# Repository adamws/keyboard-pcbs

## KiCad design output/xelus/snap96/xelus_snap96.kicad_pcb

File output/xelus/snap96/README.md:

## xelus/snap96/xelus_snap96

[layout](xelus_snap96-kle.json) - [PCB](xelus_snap96.kicad_pcb)

{:loading="lazy"}

[Open in keyboard-layout-editor](http://www.keyboard-layout-editor.com/##@_name=Snap96;&@_x:2.75&y:1&c=#888888;&=0,0&_c=#aaaaaa;&=0,1&=0,2&=0,3&=0,4&=0,5&=0,6&=0,7&=0,8&=0,9&=6,0&=6,1&=6,2&=6,3&=6,4&=6,5&=6,6&=6,7&=6,8;&@_x:2.75&c=#cccccc;&=1,0&=1,1&=1,2&=1,3&=1,4&=1,5&=1,6&=1,7&=1,8&=1,9&=7,0&=7,1&=7,2&_c=#aaaaaa&w:2;&=7,4%0A%0A%0A0,0&=7,5&=7,6&=7,7&=7,8;&@_x:2.75&w:1.5;&=2,0&_c=#cccccc;&=2,1&=2,2&=2,3&=2,4&=2,5&=2,6&=2,7&=2,8&=2,9&=8,0&=8,1&=8,2&_w:1.5;&=8,4%0A%0A%0A1,0&=8,5&=8,6&=8,7&_c=#aaaaaa&h:2;&=9,8%0A%0A%0A5,0;&@_x:2.75&w:1.75;&=3,0&_c=#cccccc;&=3,1&=3,2&=3,3&=3,4&=3,5&=3,6&=3,7&=3,8&=3,9&=9,0&=9,1&_c=#888888&w:2.25;&=9,3%0A%0A%0A1,0&_c=#cccccc;&=9,5&=9,6&=9,7;&@_x:2.75&c=#aaaaaa&w:2.25;&=4,0%0A%0A%0A2,0&_c=#cccccc;&=4,2&=4,3&=4,4&=4,5&=4,6&=4,7&=4,8&=4,9&=10,0&=10,1%0A%0A%0A3,0&_c=#aaaaaa&w:1.75;&=10,3%0A%0A%0A3,0&=10,4%0A%0A%0A3,0&_c=#cccccc;&=10,5&=10,6&=10,7&_c=#888888&h:2;&=11,8%0A%0A%0A6,0;&@_x:2.75&c=#aaaaaa&w:1.5;&=5,0%0A%0A%0A4,0&=5,1%0A%0A%0A4,0&_w:1.5;&=5,2%0A%0A%0A4,0&_c=#cccccc&w:7;&=5,6%0A%0A%0A4,0&_c=#aaaaaa&w:1.5;&=11,1%0A%0A%0A4,0&=11,3%0A%0A%0A4,0&_w:1.5;&=11,4%0A%0A%0A4,0&_c=#cccccc;&=11,5%0A%0A%0A7,0&=11,6%0A%0A%0A7,0&=11,7%0A%0A%0A7,0;&@_x:15.75&y:-7;&=7,3%0A%0A%0A0,1&=7,4%0A%0A%0A0,1;&@_x:23.25&y:1&c=#888888&w:1.25&h:2&w2:1.5&h2:1&x2:-0.25;&=8,4%0A%0A%0A1,1;&@_x:22.25&c=#cccccc;&=9,3%0A%0A%0A1,1&_x:3.25&c=#aaaaaa;&=8,8%0A%0A%0A5,1;&@_x:22.25&c=#cccccc;&=10,1%0A%0A%0A3,1&_c=#aaaaaa&w:2.75;&=10,3%0A%0A%0A3,1&_x:0.5;&=8,9%0A%0A%0A5,1;&@_w:1.25;&=4,0%0A%0A%0A2,1&_c=#cccccc;&=4,1%0A%0A%0A2,1&_x:20.0&c=#aaaaaa&w:1.75;&=10,1%0A%0A%0A3,2&_c=#cccccc;&=10,3%0A%0A%0A3,2&=10,4%0A%0A%0A3,2&_x:0.5&c=#aaaaaa;&=10,8%0A%0A%0A6,1;&@_x:26.5;&=11,8%0A%0A%0A6,1;&@_x:2.75&y:0.5&w:1.25;&=5,0%0A%0A%0A4,1&_w:1.25;&=5,1%0A%0A%0A4,1&_w:1.25;&=5,2%0A%0A%0A4,1&_c=#cccccc&w:6.25;&=5,6%0A%0A%0A4,1&_c=#aaaaaa&w:1.25;&=11,0%0A%0A%0A4,1&_w:1.25;&=11,1%0A%0A%0A4,1&_w:1.25;&=11,3%0A%0A%0A4,1&_w:1.25;&=11,4%0A%0A%0A4,1&_x:0.5&c=#cccccc&w:2;&=11,5%0A%0A%0A7,1&=11,7%0A%0A%0A7,1;&@_x:2.75&c=#aaaaaa&w:1.25;&=5,0%0A%0A%0A4,2&_w:1.25;&=5,1%0A%0A%0A4,2&_w:1.25;&=5,2%0A%0A%0A4,2&_c=#cccccc&w:2.75;&=5,5%0A%0A%0A4,2&_w:1.25;&=5,6%0A%0A%0A4,2&_w:2.25;&=5,9%0A%0A%0A4,2&_c=#aaaaaa&w:1.25;&=11,0%0A%0A%0A4,2&_w:1.25;&=11,1%0A%0A%0A4,2&_w:1.25;&=11,3%0A%0A%0A4,2&_w:1.25;&=11,4%0A%0A%0A4,2&_x:0.5&c=#cccccc;&=11,5%0A%0A%0A7,2&_w:2;&=11,7%0A%0A%0A7,2;&@_x:2.75&c=#aaaaaa&w:1.25;&=5,0%0A%0A%0A4,3&_w:1.25;&=5,1%0A%0A%0A4,3&_w:1.25;&=5,2%0A%0A%0A4,3&_c=#cccccc&w:2.25;&=5,5%0A%0A%0A4,3&_w:1.25;&=5,6%0A%0A%0A4,3&_w:2.75;&=5,9%0A%0A%0A4,3&_c=#aaaaaa&w:1.25;&=11,0%0A%0A%0A4,3&_w:1.25;&=11,1%0A%0A%0A4,3&_w:1.25;&=11,3%0A%0A%0A4,3&_w:1.25;&=11,4%0A%0A%0A4,3)

{:loading="lazy"}

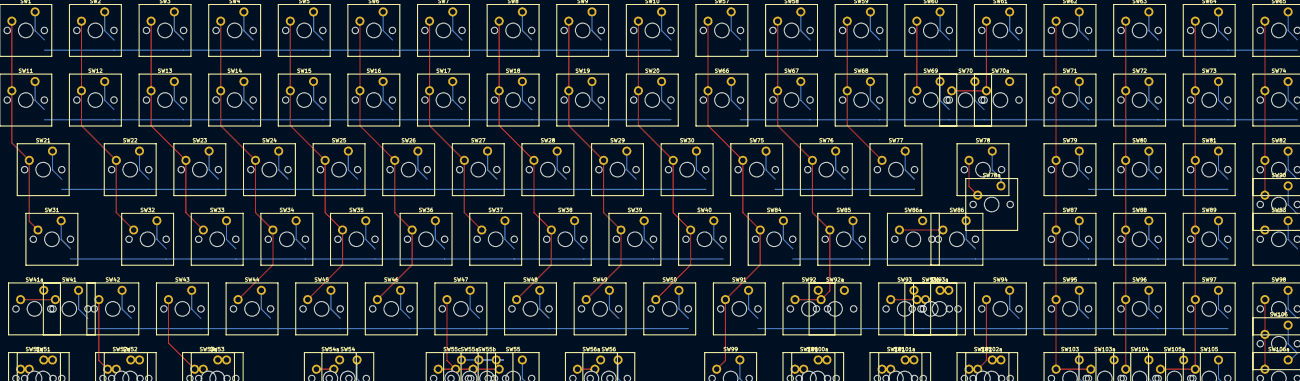
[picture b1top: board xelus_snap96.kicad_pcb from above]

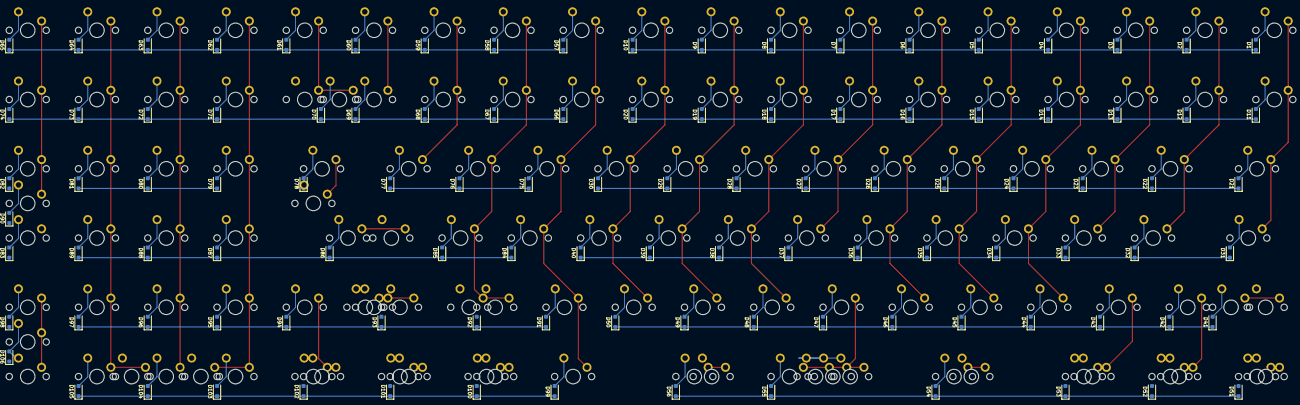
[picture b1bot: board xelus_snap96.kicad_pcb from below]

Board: 2 copper layers, 233 parts (106 on the bottom side), 128 nets.

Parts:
D1, D2, D3, D4, D5, D6, D7, D8, D9, D10, D11, D12, D13, D14, D15, D16, D17, D18, D19, D20, D21, D22, D23, D24, D25, D26, D27, D28, D29, D30, D31, D32, D33, D34, D35, D36, D37, D38, D39, D40, D41, D42, D43, D44, D45, D46, D47, D48, D49, D50, D51, D52, D53, D54, D55, D56, D57, D58, D59, D60, D61, D62, D63, D64, D65, D66, D67, D68, D69, D70, D71, D72, D73, D74, D75, D76, D77, D78, D79, D80, D81, D82, D83, D84, D85, D86, D87, D88, D89, D90, D91, D92, D93, D94, D95, D96, D97, D98, D99, D100, D101, D102, D103, D104, D105, D106: D_SOD-123F
SW1, SW2, SW3, SW4, SW5, SW6, SW7, SW8, SW9, SW10, SW11, SW12, SW13, SW14, SW15, SW16, SW17, SW18, SW19, SW20, SW21, SW22, SW23, SW24, SW25, SW26, SW27, SW28, SW29, SW30, SW31, SW32, SW33, SW34, SW35, SW36, SW37, SW38, SW39, SW40, SW41, SW41a, SW42, SW43, SW44, SW45, SW46, SW47, SW48, SW49, SW50, SW51, SW51a, SW52, SW52a, SW53, SW53a, SW54, SW54a, SW55, SW55a, SW55b, SW55c, SW56, SW56a, SW57, SW58, SW59, SW60, SW61, SW62, SW63, SW64, SW65, SW66, SW67, SW68, SW69, SW70, SW70a, SW71, SW72, SW73, SW74, SW75, SW76, SW77, SW78, SW78a, SW79, SW80, SW81, SW82, SW83, SW84, SW85, SW86, SW86a, SW87, SW88, SW89, SW90, SW91, SW92, SW92a, SW93, SW93a, SW93b, SW94, SW95, SW96, SW97, SW98, SW99, SW100, SW100a, SW101, SW101a, SW102, SW102a, SW103, SW103a, SW104, SW105, SW105a, SW106, SW106a: SW_Cherry_MX_PCB_1.00u

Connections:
COL0: SW1.1, SW11.1, SW21.1, SW31.1, SW41.1, SW41a.1, SW51.1, SW51a.1, SW57.1, SW66.1, SW75.1, SW84.1, SW91.1, SW99.1
COL1: SW2.1, SW12.1, SW22.1, SW32.1, SW42.1, SW52.1, SW52a.1, SW58.1, SW67.1, SW76.1, SW85.1, SW92.1, SW92a.1, SW100.1, SW100a.1
COL2: SW3.1, SW13.1, SW23.1, SW33.1, SW43.1, SW53.1, SW53a.1, SW59.1, SW68.1, SW77.1
COL3: SW4.1, SW14.1, SW24.1, SW34.1, SW44.1, SW60.1, SW69.1, SW86.1, SW86a.1, SW93.1, SW93a.1, SW93b.1, SW101.1, SW101a.1
COL4: SW5.1, SW15.1, SW25.1, SW35.1, SW45.1, SW61.1, SW70.1, SW70a.1, SW78.1, SW78a.1, SW94.1, SW102.1, SW102a.1
COL5: SW6.1, SW16.1, SW26.1, SW36.1, SW46.1, SW54.1, SW54a.1, SW62.1, SW71.1, SW79.1, SW87.1, SW95.1, SW103.1, SW103a.1
COL6: SW7.1, SW17.1, SW27.1, SW37.1, SW47.1, SW55.1, SW55a.1, SW55b.1, SW55c.1, SW63.1, SW72.1, SW80.1, SW88.1, SW96.1, SW104.1
COL7: SW8.1, SW18.1, SW28.1, SW38.1, SW48.1, SW64.1, SW73.1, SW81.1, SW89.1, SW97.1, SW105.1, SW105a.1
COL8: SW9.1, SW19.1, SW29.1, SW39.1, SW49.1, SW65.1, SW74.1, SW82.1, SW90.1, SW98.1, SW106.1, SW106a.1
COL9: SW10.1, SW20.1, SW30.1, SW40.1, SW50.1, SW56.1, SW56a.1, SW83.1
unnamed: D1.2, SW1.2
unnamed: D2.2, SW2.2
unnamed: D3.2, SW3.2
unnamed: D4.2, SW4.2
unnamed: D5.2, SW5.2
unnamed: D6.2, SW6.2
unnamed: D7.2, SW7.2
unnamed: D8.2, SW8.2
unnamed: D9.2, SW9.2
unnamed: D10.2, SW10.2
unnamed: D11.2, SW11.2
unnamed: D12.2, SW12.2
unnamed: D13.2, SW13.2
unnamed: D14.2, SW14.2
unnamed: D15.2, SW15.2
unnamed: D16.2, SW16.2
unnamed: D17.2, SW17.2
unnamed: D18.2, SW18.2
unnamed: D19.2, SW19.2
unnamed: D20.2, SW20.2
unnamed: D21.2, SW21.2
unnamed: D22.2, SW22.2
unnamed: D23.2, SW23.2
unnamed: D24.2, SW24.2
unnamed: D25.2, SW25.2
unnamed: D26.2, SW26.2
unnamed: D27.2, SW27.2
unnamed: D28.2, SW28.2
unnamed: D29.2, SW29.2
unnamed: D30.2, SW30.2
unnamed: D31.2, SW31.2
unnamed: D32.2, SW32.2
unnamed: D33.2, SW33.2
unnamed: D34.2, SW34.2
unnamed: D35.2, SW35.2
unnamed: D36.2, SW36.2
unnamed: D37.2, SW37.2
unnamed: D38.2, SW38.2
unnamed: D39.2, SW39.2
unnamed: D40.2, SW40.2
unnamed: D41.2, SW41.2, SW41a.2
unnamed: D42.2, SW42.2
unnamed: D43.2, SW43.2
unnamed: D44.2, SW44.2
unnamed: D45.2, SW45.2
unnamed: D46.2, SW46.2
unnamed: D47.2, SW47.2
unnamed: D48.2, SW48.2
unnamed: D49.2, SW49.2
unnamed: D50.2, SW50.2
unnamed: D51.2, SW51.2, SW51a.2
unnamed: D52.2, SW52.2, SW52a.2
unnamed: D53.2, SW53.2, SW53a.2
unnamed: D54.2, SW54.2, SW54a.2
unnamed: D55.2, SW55.2, SW55a.2, SW55b.2, SW55c.2
unnamed: D56.2, SW56.2, SW56a.2
unnamed: D57.2, SW57.2
unnamed: D58.2, SW58.2
unnamed: D59.2, SW59.2
unnamed: D60.2, SW60.2
unnamed: D61.2, SW61.2
unnamed: D62.2, SW62.2
unnamed: D63.2, SW63.2
unnamed: D64.2, SW64.2
unnamed: D65.2, SW65.2
unnamed: D66.2, SW66.2
unnamed: D67.2, SW67.2
unnamed: D68.2, SW68.2
unnamed: D69.2, SW69.2
unnamed: D70.2, SW70.2, SW70a.2
unnamed: D71.2, SW71.2
unnamed: D72.2, SW72.2
unnamed: D73.2, SW73.2
unnamed: D74.2, SW74.2
unnamed: D75.2, SW75.2
unnamed: D76.2, SW76.2
unnamed: D77.2, SW77.2
unnamed: D78.2, SW78.2, SW78a.2
unnamed: D79.2, SW79.2
unnamed: D80.2, SW80.2
unnamed: D81.2, SW81.2
unnamed: D82.2, SW82.2
unnamed: D83.2, SW83.2
unnamed: D84.2, SW84.2
unnamed: D85.2, SW85.2
unnamed: D86.2, SW86.2, SW86a.2
unnamed: D87.2, SW87.2
unnamed: D88.2, SW88.2
unnamed: D89.2, SW89.2
unnamed: D90.2, SW90.2
unnamed: D91.2, SW91.2
unnamed: D92.2, SW92.2, SW92a.2
unnamed: D93.2, SW93.2, SW93a.2, SW93b.2
unnamed: D94.2, SW94.2
unnamed: D95.2, SW95.2
unnamed: D96.2, SW96.2
unnamed: D97.2, SW97.2
unnamed: D98.2, SW98.2
unnamed: D99.2, SW99.2
unnamed: D100.2, SW100.2, SW100a.2
unnamed: D101.2, SW101.2, SW101a.2
unnamed: D102.2, SW102.2, SW102a.2
unnamed: D103.2, SW103.2, SW103a.2
unnamed: D104.2, SW104.2
unnamed: D105.2, SW105.2, SW105a.2
unnamed: D106.2, SW106.2, SW106a.2
ROW0: D1.1, D2.1, D3.1, D4.1, D5.1, D6.1, D7.1, D8.1, D9.1, D10.1
ROW1: D11.1, D12.1, D13.1, D14.1, D15.1, D16.1, D17.1, D18.1, D19.1, D20.1
ROW2: D21.1, D22.1, D23.1, D24.1, D25.1, D26.1, D27.1, D28.1, D29.1, D30.1
ROW3: D31.1, D32.1, D33.1, D34.1, D35.1, D36.1, D37.1, D38.1, D39.1, D40.1
ROW4: D41.1, D42.1, D43.1, D44.1, D45.1, D46.1, D47.1, D48.1, D49.1, D50.1
ROW5: D51.1, D52.1, D53.1, D54.1, D55.1, D56.1
ROW6: D57.1, D58.1, D59.1, D60.1, D61.1, D62.1, D63.1, D64.1, D65.1
ROW7: D66.1, D67.1, D68.1, D69.1, D70.1, D71.1, D72.1, D73.1, D74.1
ROW8: D75.1, D76.1, D77.1, D78.1, D79.1, D80.1, D81.1, D82.1, D83.1
ROW9: D84.1, D85.1, D86.1, D87.1, D88.1, D89.1, D90.1
ROW10: D91.1, D92.1, D93.1, D94.1, D95.1, D96.1, D97.1, D98.1
ROW11: D99.1, D100.1, D101.1, D102.1, D103.1, D104.1, D105.1, D106.1
